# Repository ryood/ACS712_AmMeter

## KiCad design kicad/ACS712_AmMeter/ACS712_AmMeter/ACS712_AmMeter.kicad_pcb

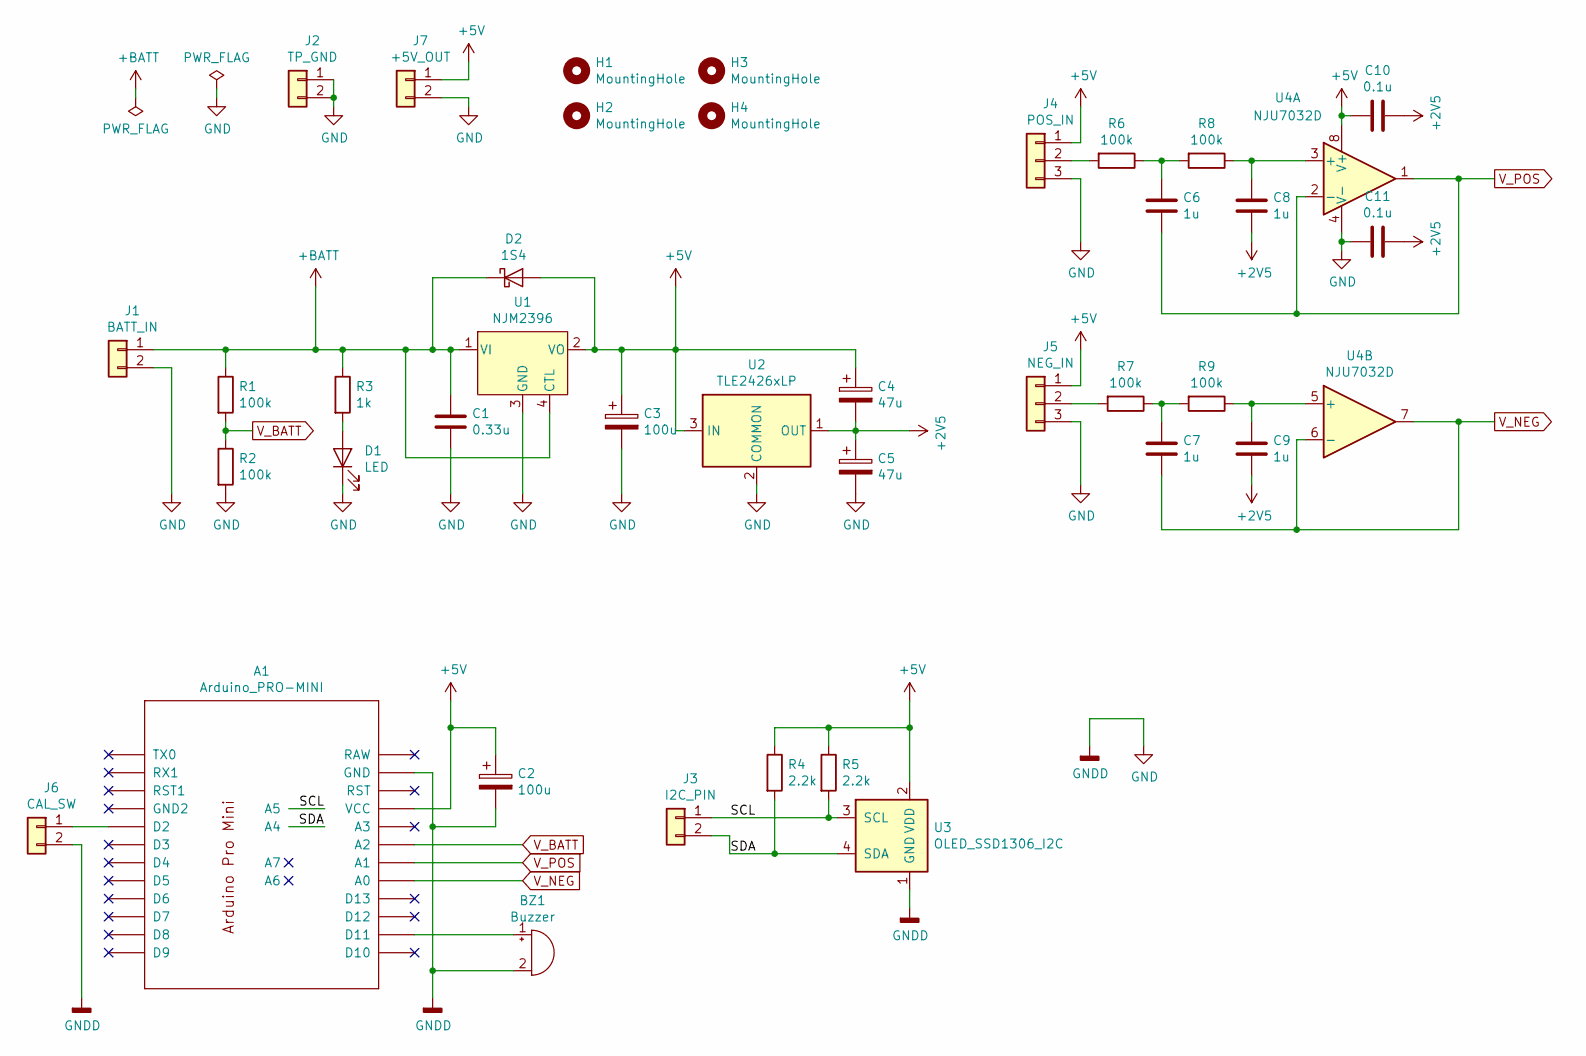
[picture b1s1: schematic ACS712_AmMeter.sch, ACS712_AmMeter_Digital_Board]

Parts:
A1: Arduino_PRO-MINI; Arduino-PRO-MINI-2-simple
BZ1: Buzzer; Buzzer_12x9.5RM7.6
C1: 0.33u; C_Disc_D5.0mm_W2.5mm_P5.00mm
C2: 100u; CP_Radial_D6.3mm_P2.50mm
C3: 100u; CP_Radial_D7.5mm_P2.50mm
C4, C5: 47u; CP_Radial_D7.5mm_P2.50mm
C6, C7, C8, C9: 1u; C_Rect_L7.0mm_W6.0mm_P5.00mm
C10, C11: 0.1u; C_Disc_D3.0mm_W2.0mm_P2.50mm
D1: LED; LED_D3.0mm
D2: 1S4; D_A-405_P10.16mm_Horizontal
H1, H2, H3, H4: MountingHole; MountingHole_3.2mm_M3
J1: BATT_IN; JST_XH_B2B-XH-A_1x02_P2.50mm_Vertical
J2: TP_GND; PinHeader_1x02_P2.54mm_Vertical
J3: I2C_PIN; PinHeader_1x02_P2.54mm_Vertical
J4: POS_IN; PinHeader_1x03_P2.54mm_Vertical
J5: NEG_IN; PinHeader_1x03_P2.54mm_Vertical
J6: CAL_SW; PinHeader_1x02_P2.54mm_Vertical
J7: +5V_OUT; PinHeader_1x02_P2.54mm_Vertical
R1, R2, R6, R7, R8, R9: 100k; R_Axial_DIN0207_L6.3mm_D2.5mm_P7.62mm_Horizontal
R3: 1k; R_Axial_DIN0207_L6.3mm_D2.5mm_P7.62mm_Horizontal
R4, R5: 2.2k; R_Axial_DIN0207_L6.3mm_D2.5mm_P7.62mm_Horizontal
U1: NJM2396; NJM2396_Vertical
U2: TLE2426xLP; TO-92_Inline_Wide
U3: OLED_SSD1306_I2C
U4: NJU7032D; DIP-8_W7.62mm

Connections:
+2V5: C4.2, C5.1, C8.2, C9.2, C10.1, C11.1, U2.1 (OUT)
+5V: A1.VCC, C2.1, C3.1, C4.1, C10.2, D2.2 (A), J4.1, J5.1, J7.1, R4.1, R5.1, U1.2 (VO), U2.3 (IN), U3.2 (VDD), U4.8 (V+)
+BATT: C1.1, D2.1 (K), J1.1, R1.1, R3.1, U1.1 (VI), U1.4 (CTL)
/SCL: A1.A5, J3.1, R5.2, U3.3 (SCL)
/SDA: A1.A4, J3.2, R4.2, U3.4 (SDA)
GND: A1.GND, BZ1.2 (+), C1.2, C2.2, C3.2, C5.2, C11.2, D1.1 (K), J1.2, J2.1, J2.2, J4.3, J5.3, J6.2, J7.2, R2.2, U1.3 (GND), U2.2 (COMMON), U3.1 (GND), U4.4 (V-)
unnamed: A1.D2, J6.1
unnamed: A1.D11, BZ1.1 (-)
unnamed: C6.1, R6.1, R8.2
unnamed: C7.1, R7.1, R9.2
unnamed: C8.1, R8.1, U4.3 (+)
unnamed: C9.1, R9.1, U4.5 (+)
unnamed: D1.2 (A), R3.2
unnamed: J4.2, R6.2
unnamed: J5.2, R7.2
V_BATT: A1.A2, R1.2, R2.1
V_NEG: A1.A0, C7.2, U4.6 (-), U4.7
V_POS: A1.A1, C6.2, U4.1, U4.2 (-)

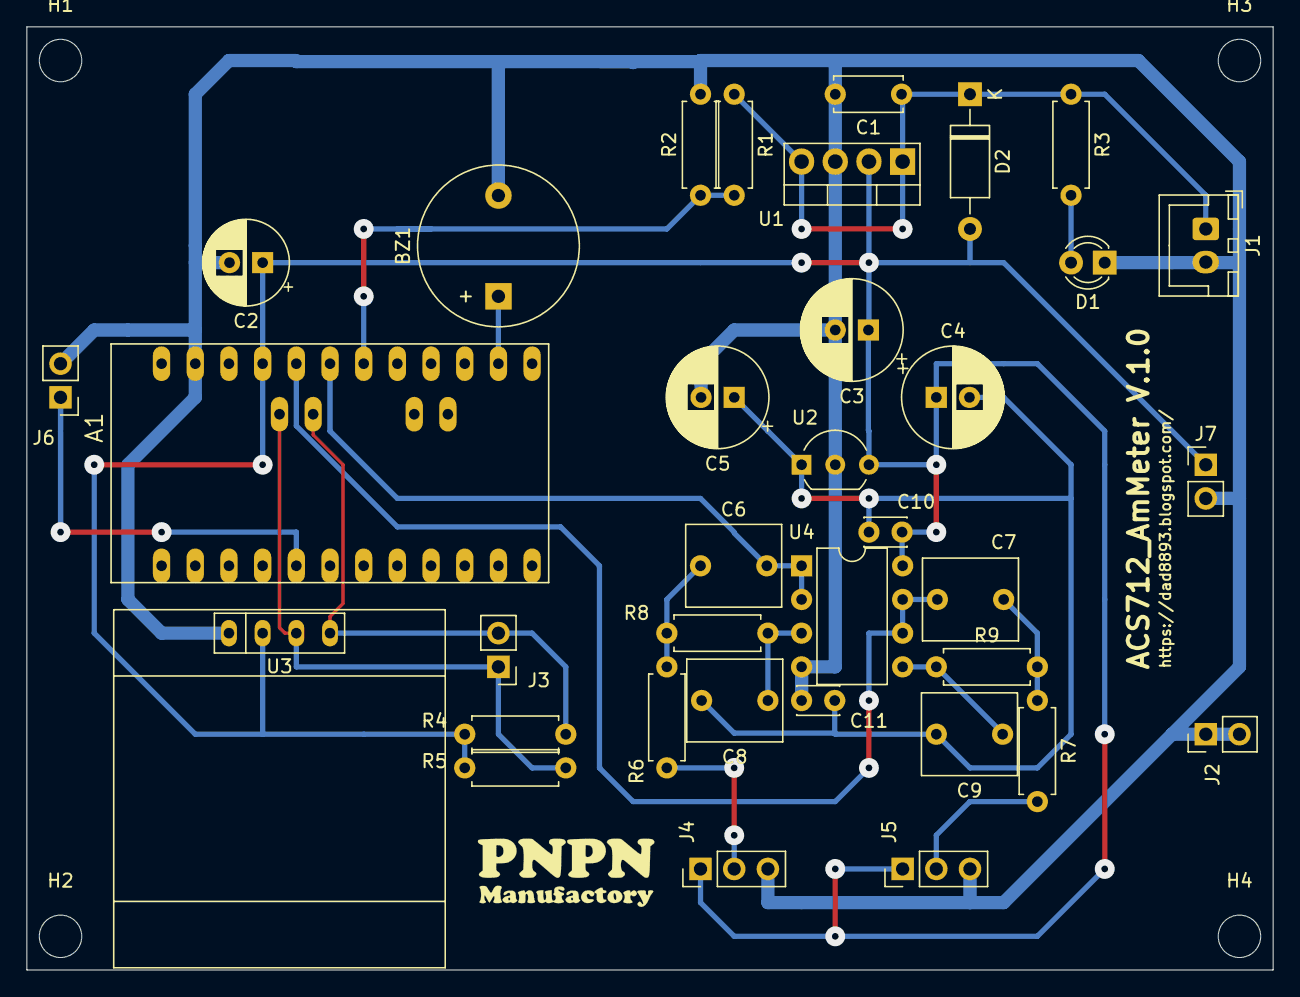
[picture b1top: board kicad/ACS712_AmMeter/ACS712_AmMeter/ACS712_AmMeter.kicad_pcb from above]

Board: 2 copper layers, 94.0 x 71.1 mm, 39 parts (0 on the bottom side), 18 nets.

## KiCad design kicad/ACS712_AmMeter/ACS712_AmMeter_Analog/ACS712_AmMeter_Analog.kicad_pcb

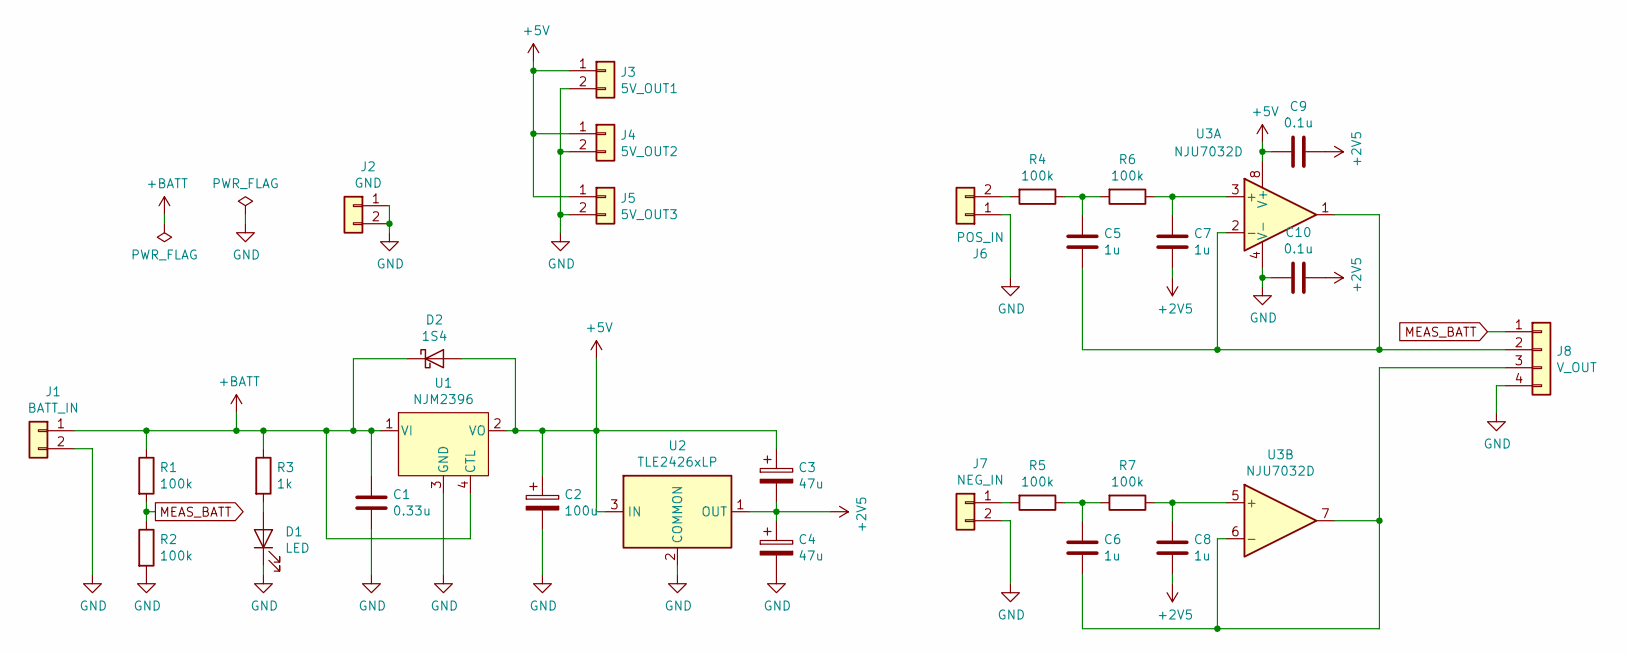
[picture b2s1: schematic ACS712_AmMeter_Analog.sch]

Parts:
C1: 0.33u; C_Disc_D5.0mm_W2.5mm_P5.00mm
C2: 100u; CP_Radial_D7.5mm_P2.50mm
C3, C4: 47u; CP_Radial_D7.5mm_P2.50mm
C5, C6, C7, C8: 1u; C_Rect_L7.0mm_W6.0mm_P5.00mm
C9, C10: 0.1u; C_Disc_D3.0mm_W2.0mm_P2.50mm
D1: LED; LED_D3.0mm
D2: 1S4; D_A-405_P10.16mm_Horizontal
J1: BATT_IN; PinHeader_1x02_P2.54mm_Horizontal
J2: GND; PinHeader_1x02_P2.54mm_Vertical
J3: 5V_OUT1; PinHeader_1x02_P2.54mm_Horizontal
J4: 5V_OUT2; PinHeader_1x02_P2.54mm_Horizontal
J5: 5V_OUT3; PinHeader_1x02_P2.54mm_Horizontal
J6: POS_IN; PinHeader_1x02_P2.54mm_Horizontal
J7: NEG_IN; PinHeader_1x02_P2.54mm_Horizontal
J8: V_OUT; PinHeader_1x04_P2.54mm_Horizontal
R1, R2, R4, R5, R6, R7: 100k; R_Axial_DIN0207_L6.3mm_D2.5mm_P7.62mm_Horizontal
R3: 1k; R_Axial_DIN0207_L6.3mm_D2.5mm_P7.62mm_Horizontal
U1: NJM2396; TO-220-4_Horizontal_TabDown
U2: TLE2426xLP; TO-92_Inline_Wide
U3: NJU7032D; DIP-8_W7.62mm

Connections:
+2V5: C3.2, C4.1, C7.2, C8.2, C9.1, C10.1, U2.1 (OUT)
+5V: C2.1, C3.1, C9.2, D2.2 (A), J3.1, J4.1, J5.1, U1.2 (VO), U2.3 (IN), U3.8 (V+)
+BATT: C1.1, D2.1 (K), J1.1, R1.1, R3.1, U1.1 (VI), U1.4 (CTL)
GND: C1.2, C2.2, C4.2, C10.2, D1.1 (K), J1.2, J2.1, J2.2, J3.2, J4.2, J5.2, J6.1, J7.2, J8.4, R2.2, U1.3 (GND), U2.2 (COMMON), U3.4 (V-)
MEAS_BATT: J8.1, R1.2, R2.1
unnamed: C5.1, R4.1, R6.2
unnamed: C5.2, J8.2, U3.1, U3.2 (-)
unnamed: C6.1, R5.1, R7.2
unnamed: C6.2, J8.3, U3.6 (-), U3.7
unnamed: C7.1, R6.1, U3.3 (+)
unnamed: C8.1, R7.1, U3.5 (+)
unnamed: D1.2 (A), R3.2
unnamed: J6.2, R4.2
unnamed: J7.1, R5.2

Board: 2 copper layers, 30 parts (0 on the bottom side), 14 nets, no tracks yet.

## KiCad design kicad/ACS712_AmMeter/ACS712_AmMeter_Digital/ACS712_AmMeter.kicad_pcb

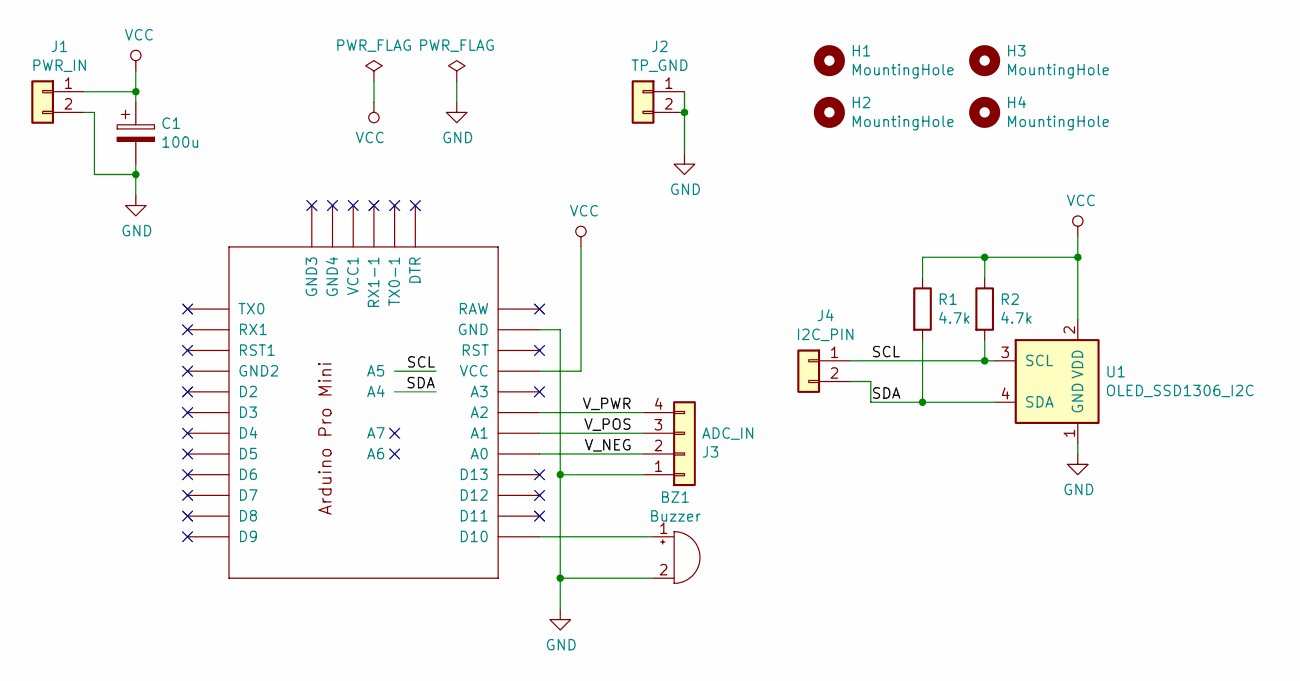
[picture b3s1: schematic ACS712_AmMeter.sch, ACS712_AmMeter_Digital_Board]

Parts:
A1: Arduino_PRO-MINI-2; PRO-MINI-2
BZ1: Buzzer; Buzzer_12x9.5RM7.6
C1: 100u; CP_Radial_D6.3mm_P2.50mm
H1, H2, H3, H4: MountingHole; MountingHole_3.2mm_M3
J1: PWR_IN; PinHeader_1x02_P2.54mm_Horizontal
J2: TP_GND; PinHeader_1x02_P2.54mm_Vertical
J3: ADC_IN; PinHeader_1x04_P2.54mm_Horizontal
J4: I2C_PIN; PinSocket_1x02_P2.54mm_Vertical
R1, R2: 4.7k; R_Axial_DIN0207_L6.3mm_D2.5mm_P7.62mm_Horizontal
U1: OLED_SSD1306_I2C

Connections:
/SCL: A1.A5, J4.1, R2.2, U1.3 (SCL)
/SDA: A1.A4, J4.2, R1.2, U1.4 (SDA)
/V_NEG: A1.A0, J3.2
/V_POS: A1.A1, J3.3
/V_PWR: A1.A2, J3.4
GND: A1.GND, BZ1.2 (+), C1.2, J1.2, J2.1, J2.2, J3.1, U1.1 (GND)
unnamed: A1.D10, BZ1.1 (-)
VCC: A1.VCC, C1.1, J1.1, R1.1, R2.1, U1.2 (VDD)

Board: 2 copper layers, 14 parts (0 on the bottom side), 8 nets, no tracks yet.

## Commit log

2020-01-03 Update: VCVS LPF
2020-01-09 Add: Arduino Sketch
2020-01-18 Add: KiCad design
2020-01-20 Update: integrate digital and analog
2020-01-20 Update: Arduino sketch
2020-01-22 Add: logo bule, Update: KiCad design
2020-01-25 Update: Board design
2020-01-29 Ubdate: Board design
2020-02-06 Soldering completed
2020-03-01 Bugfix: Arduino sketch
